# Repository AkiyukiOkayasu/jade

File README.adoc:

= jade
:lang: en
:doctype: book
:author: Akiyuki Okayasu
:revnumber: 0.1
:icons: font
:scripts: cjk
:pdf-fontsdir: ./fonts
:pdf-style: ./theme/theme_pdf.yml
ifdef::env-github[]
:tip-caption: :bulb:
:note-caption: :information_source:
:important-caption: :heavy_exclamation_mark:
:caution-caption: :fire:
:warning-caption: :warning:
endif::[]

USB-MIDI to monome ii converter. +
Use MIDI SysEx to communicate with monome ii. +
It should be noted that this project is in its early stages.

== Dependencies
* Platform IO

== Document
https://akiyukiokayasu.github.io/jade/[document]

== Data format
SysEx can only send values between 0 and 127. Therefore, 1 byte (0~255) of monome ii is divided into 2 bytes and sent. +
Like this. +

Original data (1byte):: |ABCDEFGH|
Divide data (2bytes):: |0000ABCD| |0000EFGH|

== Hardware
The Eurorack module is being designed. 

== Max for Live
Creating dedicated Max for live devices. + 

== LICENSE
MIT +
link:LICENSE[LICENSE]

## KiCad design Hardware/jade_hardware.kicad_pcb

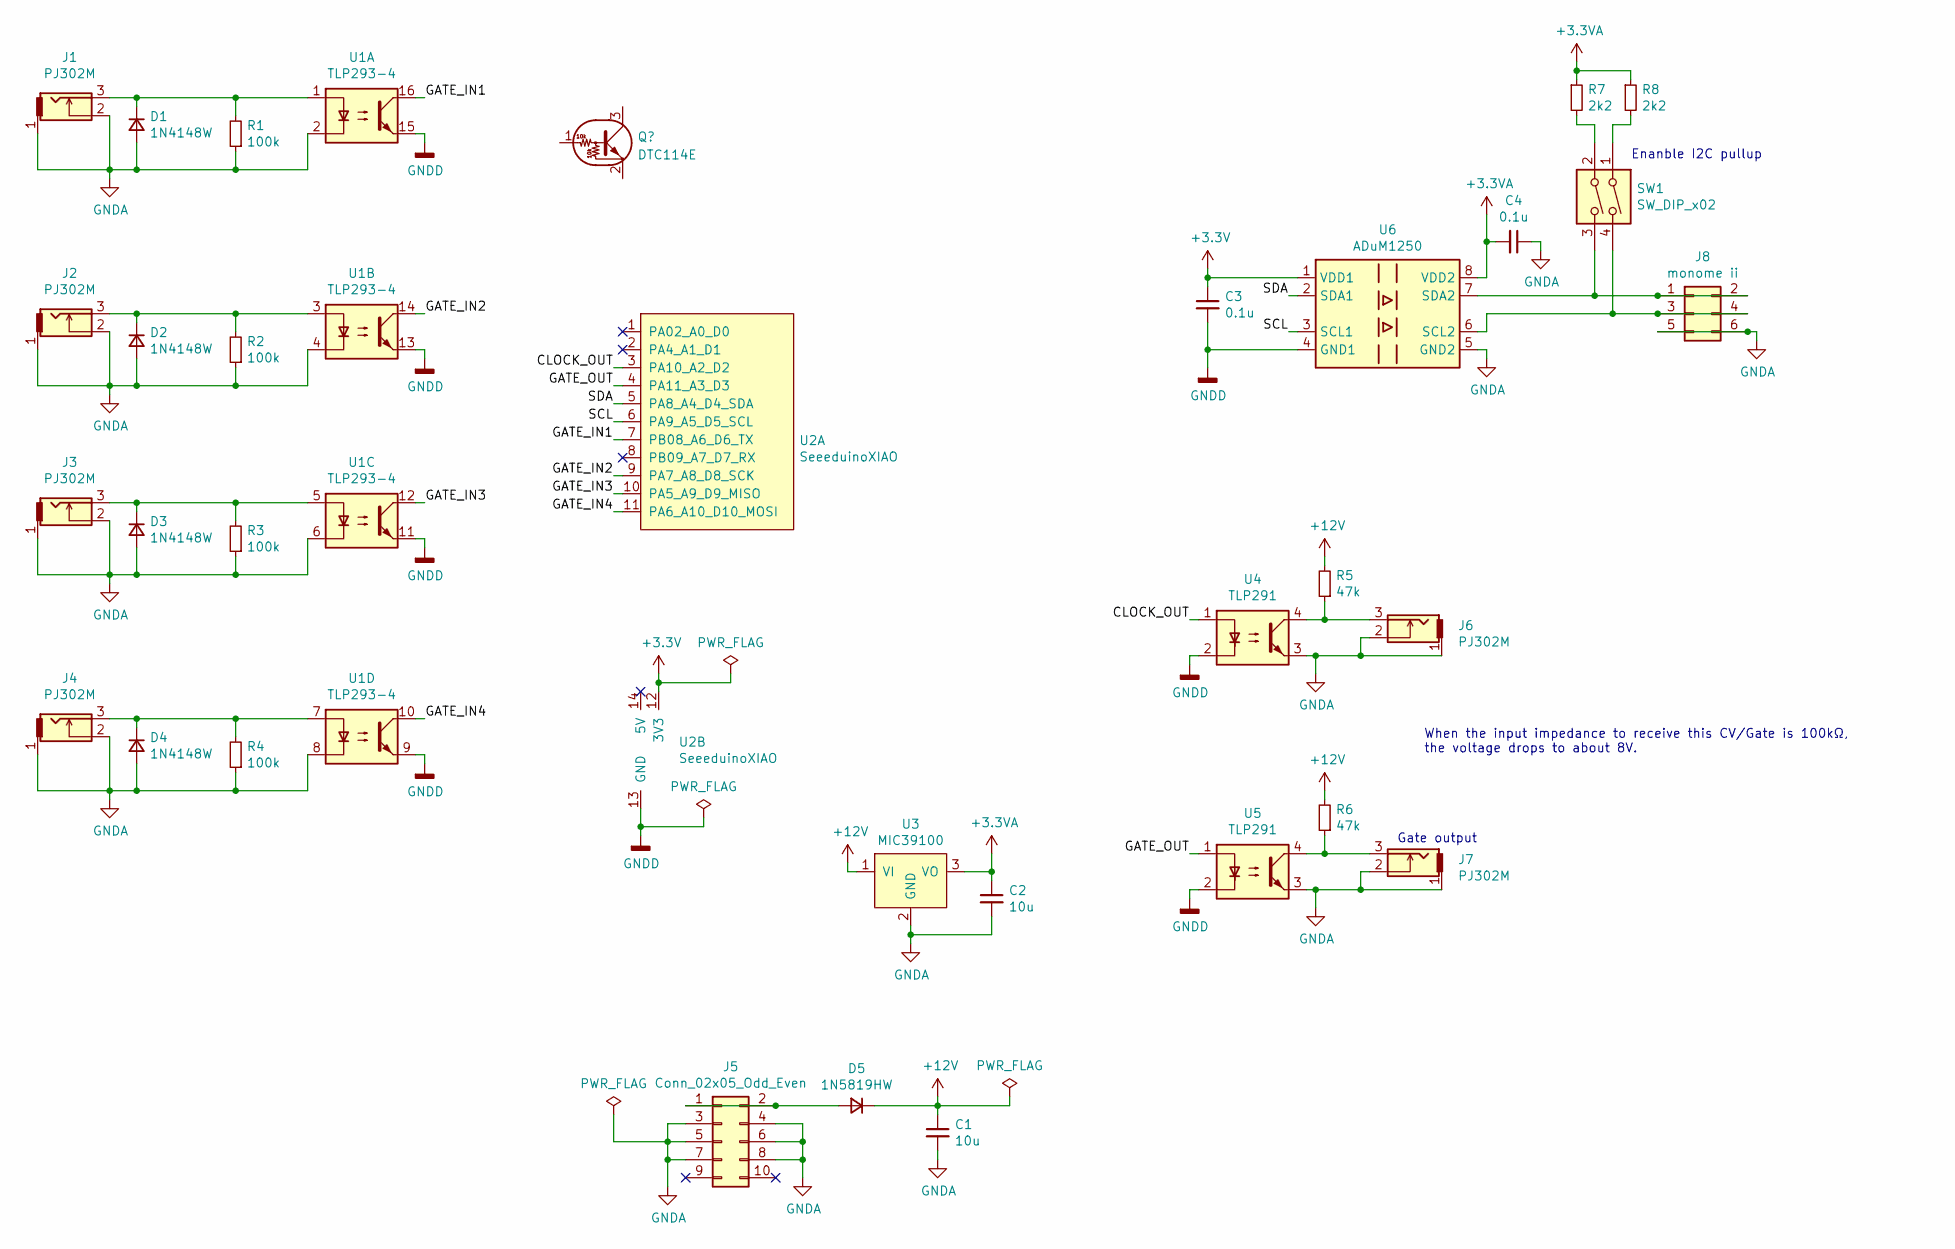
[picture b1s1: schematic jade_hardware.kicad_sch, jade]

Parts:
C1, C2: 10u; C_0805_2012Metric_Pad1.18x1.45mm_HandSolder
C3, C4: 0.1u; C_0402_1005Metric_Pad0.74x0.62mm_HandSolder
D1, D2, D3, D4: 1N4148W; D_SOD-123
D5: 1N5819HW; D_SOD-123
J1, J2, J3, J4, J6, J7: PJ302M
J5: Conn_02x05_Odd_Even; PinHeader_2x05_P2.54mm_Horizontal
J8: monome ii; PinHeader_2x03_P2.54mm_Horizontal
R1, R2, R3, R4: 100k; R_0402_1005Metric_Pad0.72x0.64mm_HandSolder
R5, R6: 47k; R_0402_1005Metric_Pad0.72x0.64mm_HandSolder
R7, R8: 2k2; R_0402_1005Metric_Pad0.72x0.64mm_HandSolder
SW1: SW_DIP_x02; OTAX_KHS_2
U1: TLP293-4; SOIC-16_4.55x10.3mm_P1.27mm
U2: SeeeduinoXIAO; Seeeduino_XIAO_NonBottomPad
U3: MIC39100; SOT-223-3_TabPin2
U4, U5: TLP291; SOIC-4_4.55x2.6mm_P1.27mm
U6: ADuM1250; SOIC-8_3.9x4.9mm_P1.27mm

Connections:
+3.3VA: C2.1, C4.2, R7.1, R8.1, U3.3 (VO), U6.8 (VDD2)
+3V3: C3.1, U2.12 (3V3), U6.1 (VDD1)
+12V: C1.1, D5.1 (K), R5.2, R6.2, U3.1 (VI)
/CLOCK_OUT: U2.3 (PA10_A2_D2), U4.1
/GATE_IN1: U1.16, U2.7 (PB08_A6_D6_TX)
/GATE_IN2: U1.14, U2.9 (PA7_A8_D8_SCK)
/GATE_IN3: U1.12, U2.10 (PA5_A9_D9_MISO)
/GATE_IN4: U1.10, U2.11 (PA6_A10_D10_MOSI)
/GATE_OUT: U2.4 (PA11_A3_D3), U5.1
/SCL: U2.6 (PA9_A5_D5_SCL), U6.3 (SCL1)
/SDA: U2.5 (PA8_A4_D4_SDA), U6.2 (SDA1)
GNDA: C1.2, C2.2, C4.1, D1.2 (A), D2.2 (A), D3.2 (A), D4.2 (A), J1.1, J1.2, J2.1, J2.2, J3.1, J3.2, J4.1, J4.2, J5.3, J5.4, J5.5, J5.6, J5.7, J5.8, J6.1, J6.2, J7.1, J7.2, J8.5, J8.6, R1.1, R2.1, R3.1, R4.1, U1.2, U1.4, U1.6, U1.8, U3.2 (GND), U4.3, U5.3, U6.5 (GND2)
GNDD: C3.2, U1.9, U1.11, U1.13, U1.15, U2.13 (GND), U4.2, U5.2, U6.4 (GND1)
unnamed: D1.1 (K), J1.3, R1.2, U1.1
unnamed: D2.1 (K), J2.3, R2.2, U1.3
unnamed: D3.1 (K), J3.3, R3.2, U1.5
unnamed: D4.1 (K), J4.3, R4.2, U1.7
unnamed: D5.2 (A), J5.1, J5.2
unnamed: J6.3, R5.1, U4.4
unnamed: J7.3, R6.1, U5.4
unnamed: J8.1, J8.2, SW1.3, U6.7 (SDA2)
unnamed: J8.3, J8.4, SW1.4, U6.6 (SCL2)
unnamed: R7.2, SW1.2
unnamed: R8.2, SW1.1

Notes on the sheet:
When the input impedance to receive this CV/Gate is 100kΩ, the voltage drops to about 8V.
Enanble I2C pullup
Gate output

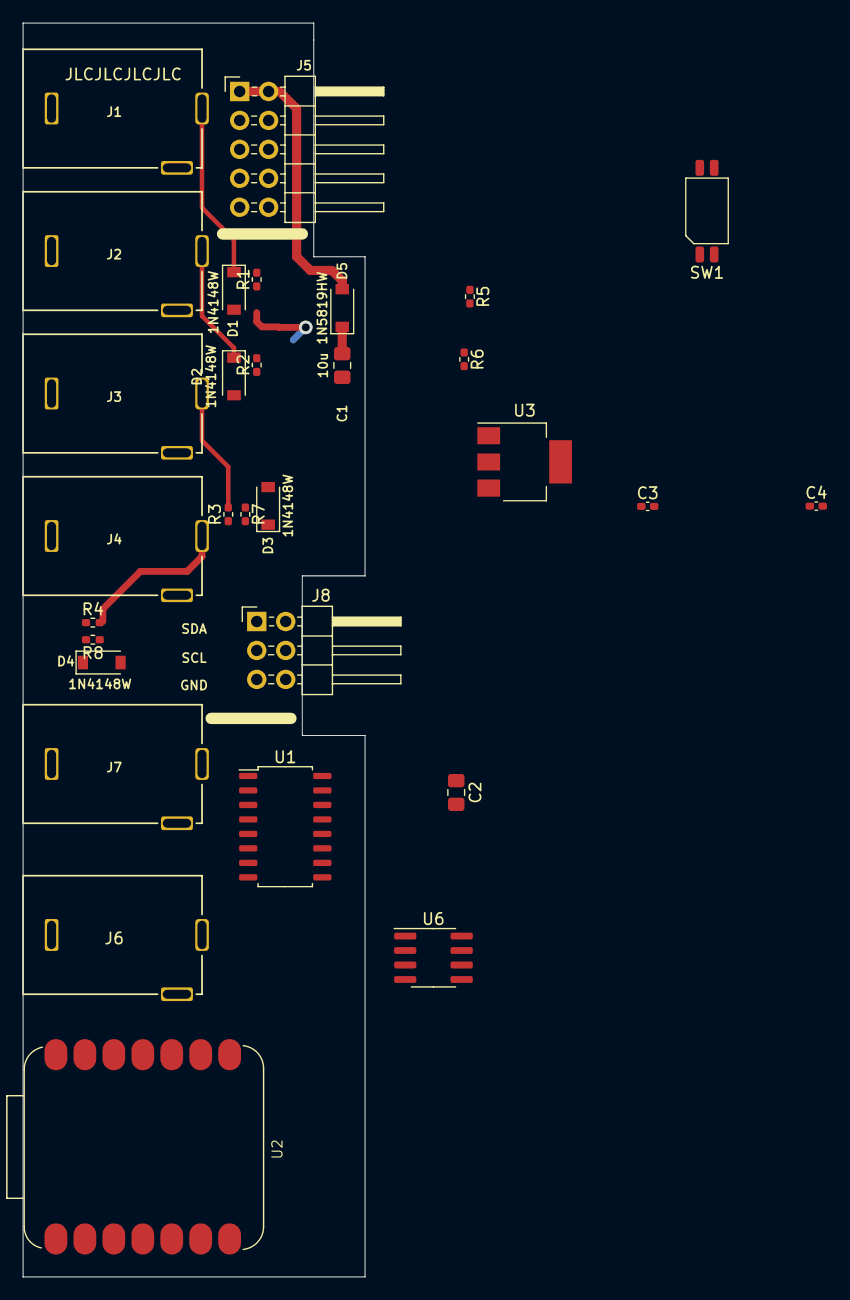
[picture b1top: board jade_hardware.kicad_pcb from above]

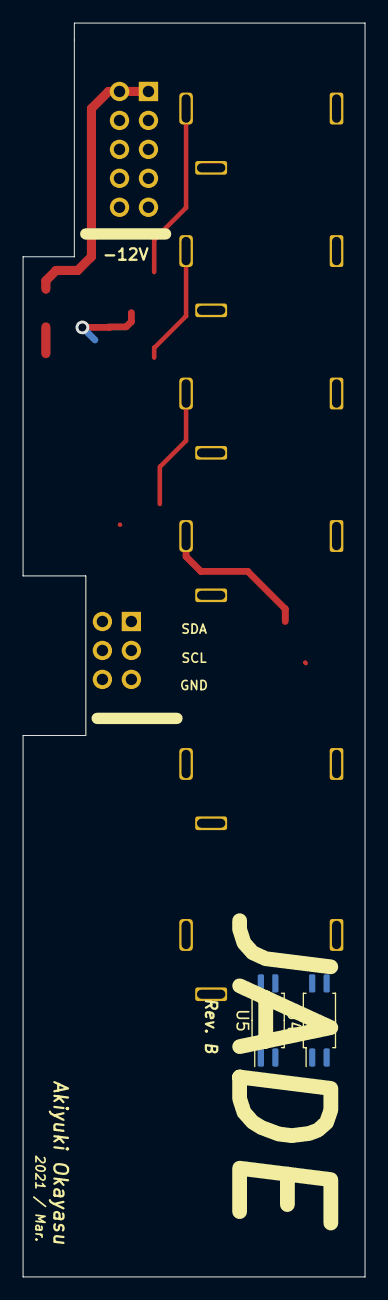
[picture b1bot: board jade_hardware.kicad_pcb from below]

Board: 2 copper layers, 30.0 x 110.0 mm, 32 parts (2 on the bottom side), 24 nets.

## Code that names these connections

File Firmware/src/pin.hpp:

/** 
    Constants about Seeeduino XAIO GPIO.
    @file pin.hpp
    @author Akiyuki Okayasu (akiyuki.okayasu@gmail.com)
    @copyright Copyright (c) 2021 - Akiyuki Okayasu    
*/

#pragma once

namespace pin
{
constexpr uint8_t LED = 13;
constexpr uint8_t I2C_SDA = 4;
constexpr uint8_t I2C_SCL = 5;
constexpr uint8_t CLOCK_OUT = 3; ///< D3
constexpr uint8_t GATE_OUT = 2;  ///< D2
constexpr uint8_t GATE_IN1 = 6;  ///< D6
constexpr uint8_t GATE_IN2 = 8;  ///< D8
constexpr uint8_t GATE_IN3 = 9;  ///< D9
constexpr uint8_t GATE_IN4 = 10; ///< D10
} // namespace pin

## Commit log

2020-11-11 Add: platformio.ini
2020-11-11 gitignore: ignore .pio/ and .vscode/
2020-11-11 Add: all files
2020-11-11 Add: pin定数を記述するヘッダーpin.hppを追加
2020-11-11 Update: LチカをMIDIParseクラスでやってみた
2020-11-12 変数名微調整
2020-11-12 Add: MIDI用コールバック関数の抽象クラス
2020-11-12 Update: noteON/OFFのコールバック関数化
2020-11-12 Add: MIDI CCのコールバック追加
2020-11-13 Remove: 使わなくなったコードを削除
2020-11-27 iiの定数ヘッダー
2020-11-27 MaxからのSerialでJF動いた
2020-11-27 コード整理
2020-11-27 Maxパッチ追加
2020-11-27 pin定数の名前空間追加
2020-11-27 pin定数の名前空間追加に伴った変更
2020-11-27 I2Cピンの内部プルアップ
2020-11-29 ボーレード更新
2020-12-01 Remove: clearSysExFlag()
2020-12-01 uint8 2つを合成する関数を追加
2020-12-01 Add: SysEx都合のバイト分割をしたバージョン
2020-12-01 不要なコメントを削除
2020-12-01 バイト分割版でもJF Voxできた
2020-12-01 JF voxのパッチ
2020-12-03 Update: メインループの遅延を50usに短縮
2020-12-03 Remove: jfSetup(), iiJF()を削除
2020-12-03 Remove: プリントを削除
2020-12-03 Update: Maxパッチ更新
2021-02-11 .clang format
2021-02-11 monome iiの定数を明確化
2021-02-11 Seeeduino XAIOのGPIO定数
2021-02-11 MIDIの定数
2021-02-11 MIDIパーサーをstd::functionなどを使って綺麗にした
2021-02-11 前回のコミットの追加忘れ
2021-02-11 main.cppにこれまでの変更を適用
2021-02-11 doxyfile
2021-02-11 doxygen
2021-02-11 Remove: max patch
2021-02-11 Create LICENSE
2021-02-11 comment
2021-02-11 Remove: 不使用のincludeを削除
2021-02-11 一部のuint_fast8_tをuint8に置き換え
2021-02-11 MIDI定数の追加
2021-02-11 MIDIParserのリファクタリング
2021-02-11 MIDIParserの更新に合わせてmainを対応
2021-02-12 Fix: pinModeでOUTPUTを指定するはずがHIGHと書いてしまっていたのを修正
    どちらも1なので問題なく動いてしまっていた
2021-02-12 Add: タイマーコールバックでクロック出力機能追加
2021-02-12 D3ピン定数を追加
2021-02-12 TC3とTC4で2系統のクロックを出力
2021-02-12 TODO タイマーのカウンターサイズを16bitに下げた
2021-02-23 Update: pin constants name
2021-02-23 remove: Timer4
2021-02-23 Update: 32bit hardware timer
2021-02-23 Update clock output gpio
2021-02-24 comments
2021-02-24 Add SysEx device id for jade
2021-02-24 TODO for sysExCallback
2021-02-24 doxyfile: add exclude some folders
2021-02-24 doxygenlayout.xml
2021-03-02 32bitタイマーでクロック出力できた
2021-03-02 MIDIノート入力ででGATE ON/OFF
2021-03-02 TODOコメント追加
2021-03-02 GPIO定数を追加（GATE_IN 1~5）
2021-03-02 コメントの集成
2021-03-02 pin5と7の割り込みは同時に使えないので、pin7を使うのをやめ、GATE_INは4個に減らした
2021-03-02 Serialのボーレートを115200に指定
2021-03-02 GateInput機能実装完了
2021-03-03 いらないプリント消した
2021-03-08 Move the platformio files to the Firmware folder
2021-03-08 Add a Hardware folder
2021-03-08 Add a Panel folder
2021-03-08 add a Max for Live folder
2021-03-08 Remove gerber files
2021-03-08 Update directory names
2021-03-08 jadeのSysEx受信部分を新しいjade用SysExフォーマットに合わせた
2021-03-08 サブパッチの名称変更 SysExTerminate→jadeSysExTerminator.maxpat
    jade用のサブコマンドが増えてSysExTerminateでは実態に則さなくなったため
2021-03-08 jade_JF_modeをスリムにし、Info Viewのコメントを記載した
2021-03-08 サブパッチの更新に追従した
2021-03-08 JF Run用のM4Lできた
2021-03-09 jade_JF_trigger.amxd v0.5.0
2021-03-09 JF vox
2021-03-09 初期値調整
2021-03-09 JF VTR微調整
2021-03-09 JF tick for Geode
2021-03-09 Add some monome ii device ID
2021-03-15 JadeのGate入力の数（4）をコンパイル時定数として定義
2021-03-15 Fixed typo
2021-03-15 MIDIコールバック関数をラムダから明示的な関数に変更
2021-03-15 USB-MIDIパケット生成用関数群を定義
2021-03-15 Gate入力のハンドラを追加
2021-03-15 GPIOのattacInteruptをFALLINGからCHANGEに変更
2021-03-15 Gate入力に応じてUSB-MIDIのnote on/offする機能を追加
2021-03-15 VSCode settings.json
2021-03-15 Remove SerialUSB
2021-03-15 format
2021-03-15 Remove useless variable
2021-03-16 JF tick v0.5.2 同期の感覚を1n~16nで選択可能にした
2021-03-16 見た目の調整 6.5pxグリッドに変更
2021-03-16 JF tick: LiveのBPMを下げた際に、同期に関係なくトリガーされてしまう問題を修正
2021-03-16 M4L全デバイスの見た目の調整
2021-03-17 Gate入力の状態遷移が行われない問題を修正
2021-03-17 Clock outとGate outのGPIOが入れ替わってたのを修正
2021-03-17 SysExの長さのassertが間違ってたのを修正
2021-03-17 JF noteとJF modeの動作確認OK
2021-03-17 デバッグ用のprint削除
2021-03-17 MIDI channel messageの定数を追加
2021-03-17 MIDI note on/offの1バイト目が間違ってたのを修正
2021-03-17 MidiUSB.flush()の位置を移動
2021-03-18 print消した
2021-03-18 jade_Clock AbletonのBPMと同じ値をjadeのClockに送信する
2021-03-19 MIDI noteのみ出力せず、その他のMIDIは素通しするやつ
2021-03-19 JF_noteとJF_voxのmidiparseの仕様？でMIDI noteが出力されなくなる問題を回避
2021-03-19 SystemRealtime用の定数を追加
2021-03-19 MIDIクロックでクロック出力はできたので、ハードウェアタイマーのライブラリを削除
2021-03-19 TODO追加 MIDIクロックのカウンター
2021-03-19 MIDI clockを受け、4分音符間隔でclockを出力する機能追加
2021-03-19 .vscode
2021-03-19 gitignore
2021-03-20 Eurorack main board Rev.B
2021-03-20 PCB Panel for Rev.B
2021-03-22 SysEx出力するM4LデバイスをAbleton Live 10.0.0以降にのみ対応とした
    Live10以前はM4LからのSysEx出力はサポートされていないため。
2021-03-22 jade_JF_runのfreeze忘れ
2021-03-23 最近のJF note, voxの変更によってSysExが出力されなくなっていた問題を修正
2021-03-23 M4L: ER-301 CV
2021-03-24 ER-301のiiコマンド定数を追加
2021-03-24 Clock出力を16分音符間隔に変更
2021-03-25 M4L: JF MPE compatible synth
2021-03-25 CV output for Ansible (teletype mode)
2021-03-26 JF_MPE_Synth freeze
2021-03-29 Remove jade_Clock.amxd
2021-05-09 Schematic Rev.C
2021-05-21 update all changes before stash
2021-08-03 Fix typo
2021-08-03 リファクタ
2022-03-03 KiCad6に移行
2026-04-13 保存し直し
2026-04-13 feat: 起動時にJFのmodeを送信する
